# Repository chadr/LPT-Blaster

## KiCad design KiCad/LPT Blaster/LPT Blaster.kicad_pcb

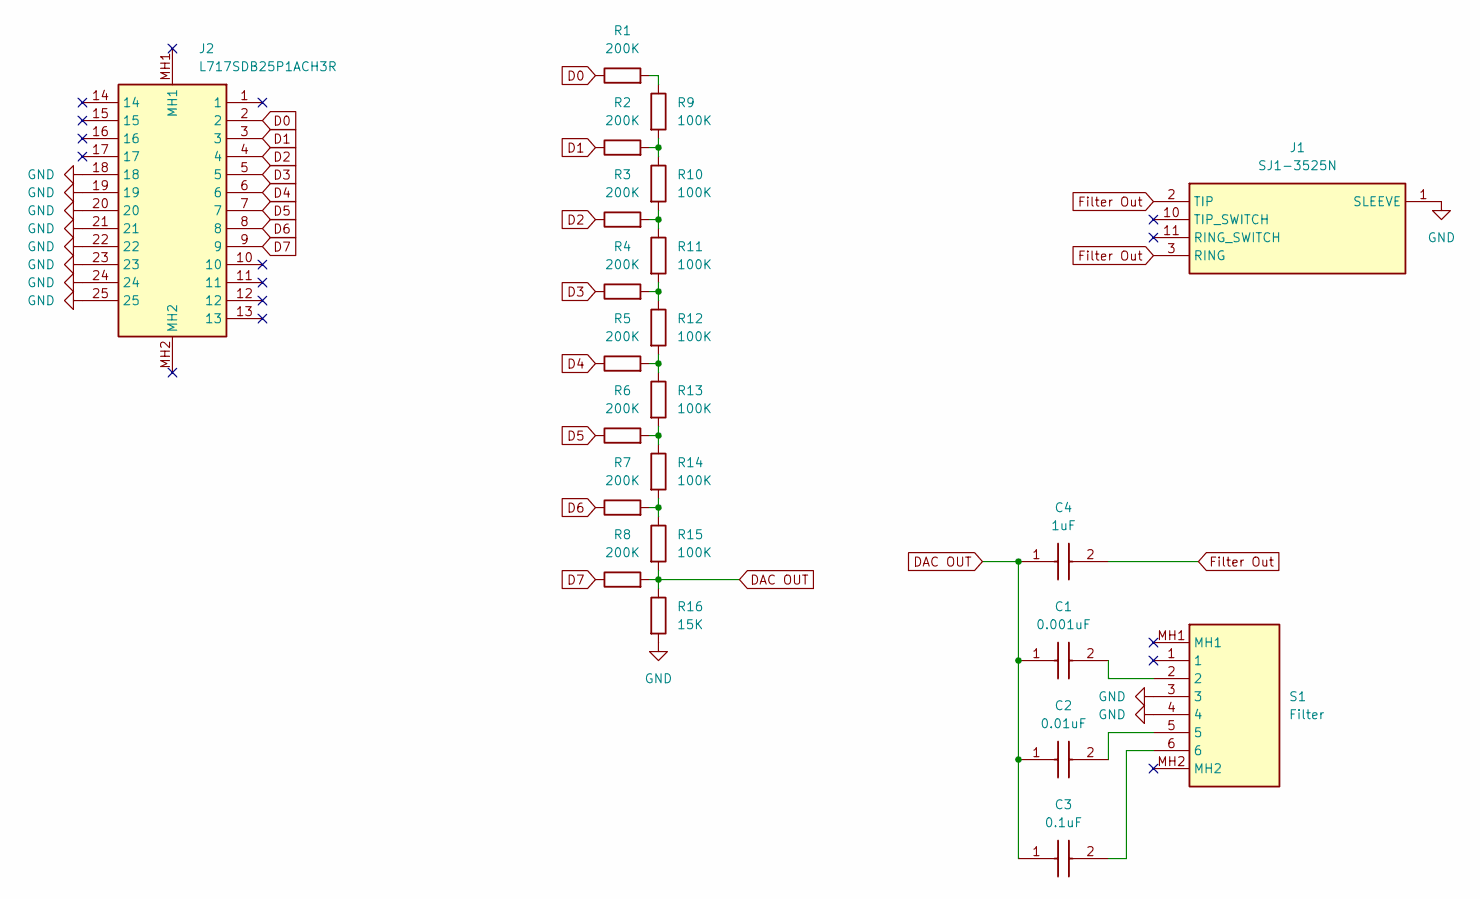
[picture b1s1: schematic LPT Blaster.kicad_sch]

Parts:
C1: 0.001uF; R82DC4100DQ60J; Manufacturer_Part_Number R82DC4100DQ60J; Mouser Part Number 80-R82DC4100DQ60J
C2: 0.01uF; R82DC4100DQ60J; Manufacturer_Part_Number R82DC4100DQ60J; Mouser Part Number 80-R82DC4100DQ60J
C3: 0.1uF; R82DC4100DQ60J; Manufacturer_Part_Number R82DC4100DQ60J; Mouser Part Number 80-R82DC4100DQ60J
C4: 1uF; R82DC4100DQ60J; Manufacturer_Part_Number R82DC4100DQ60J; Mouser Part Number 80-R82DC4100DQ60J
J1: SJ1-3525N; SJ13525N; Manufacturer_Part_Number SJ1-3525N
J2: L717SDB25P1ACH3R; Manufacturer_Part_Number L717SDB25P1ACH3R; Mouser Part Number 523-L717SDB25P1ACH3R
R1, R2, R3, R4, R5, R6, R7, R8: 200K; R_Axial_DIN0207_L6.3mm_D2.5mm_P10.16mm_Horizontal
R9, R10, R11, R12, R13, R14, R15: 100K; R_Axial_DIN0207_L6.3mm_D2.5mm_P10.16mm_Horizontal
R16: 15K; R_Axial_DIN0207_L6.3mm_D2.5mm_P10.16mm_Horizontal
S1: Filter; SK14D01G6; Manufacturer_Part_Number SK14D01G6; Mouser Part Number 611-SK-14D01-G6

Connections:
D0: J2.2, R1.1
D1: J2.3, R2.1
D2: J2.4, R3.1
D3: J2.5, R4.1
D4: J2.6, R5.1
D5: J2.7, R6.1
D6: J2.8, R7.1
D7: J2.9, R8.1
DAC OUT: C1.1, C2.1, C3.1, C4.1, R8.2, R15.2, R16.1
Filter Out: C4.2, J1.2 (TIP), J1.3 (RING)
GND: J1.1 (SLEEVE), J2.18, J2.19, J2.20, J2.21, J2.22, J2.23, J2.24, J2.25, R16.2, S1.3, S1.4
unnamed: C1.2, S1.2
unnamed: C2.2, S1.5
unnamed: C3.2, S1.6
unnamed: R1.2, R9.1
unnamed: R2.2, R9.2, R10.1
unnamed: R3.2, R10.2, R11.1
unnamed: R4.2, R11.2, R12.1
unnamed: R5.2, R12.2, R13.1
unnamed: R6.2, R13.2, R14.1
unnamed: R7.2, R14.2, R15.1

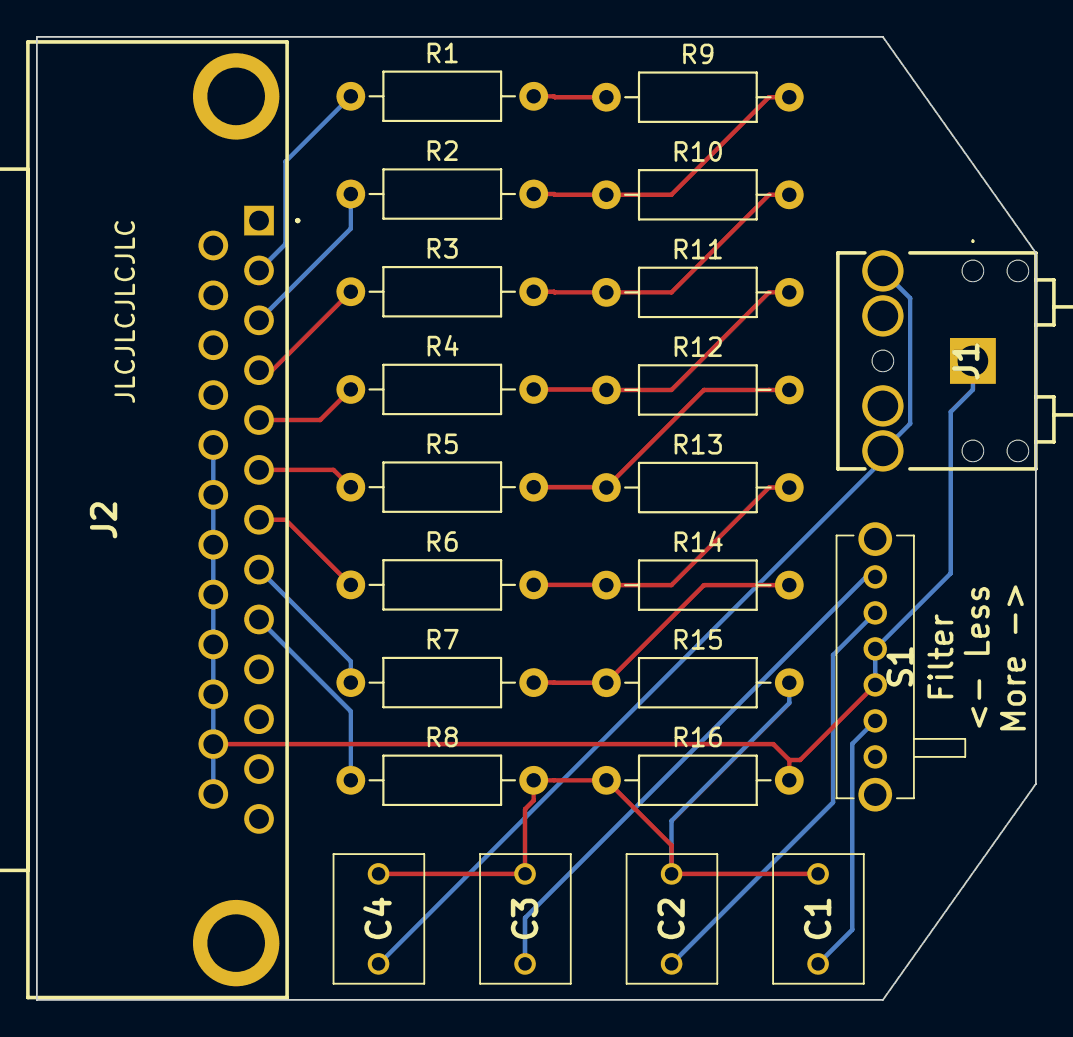
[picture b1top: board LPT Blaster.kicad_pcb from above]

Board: 2 copper layers, 55.5 x 53.5 mm, 23 parts (0 on the bottom side), 21 nets.
